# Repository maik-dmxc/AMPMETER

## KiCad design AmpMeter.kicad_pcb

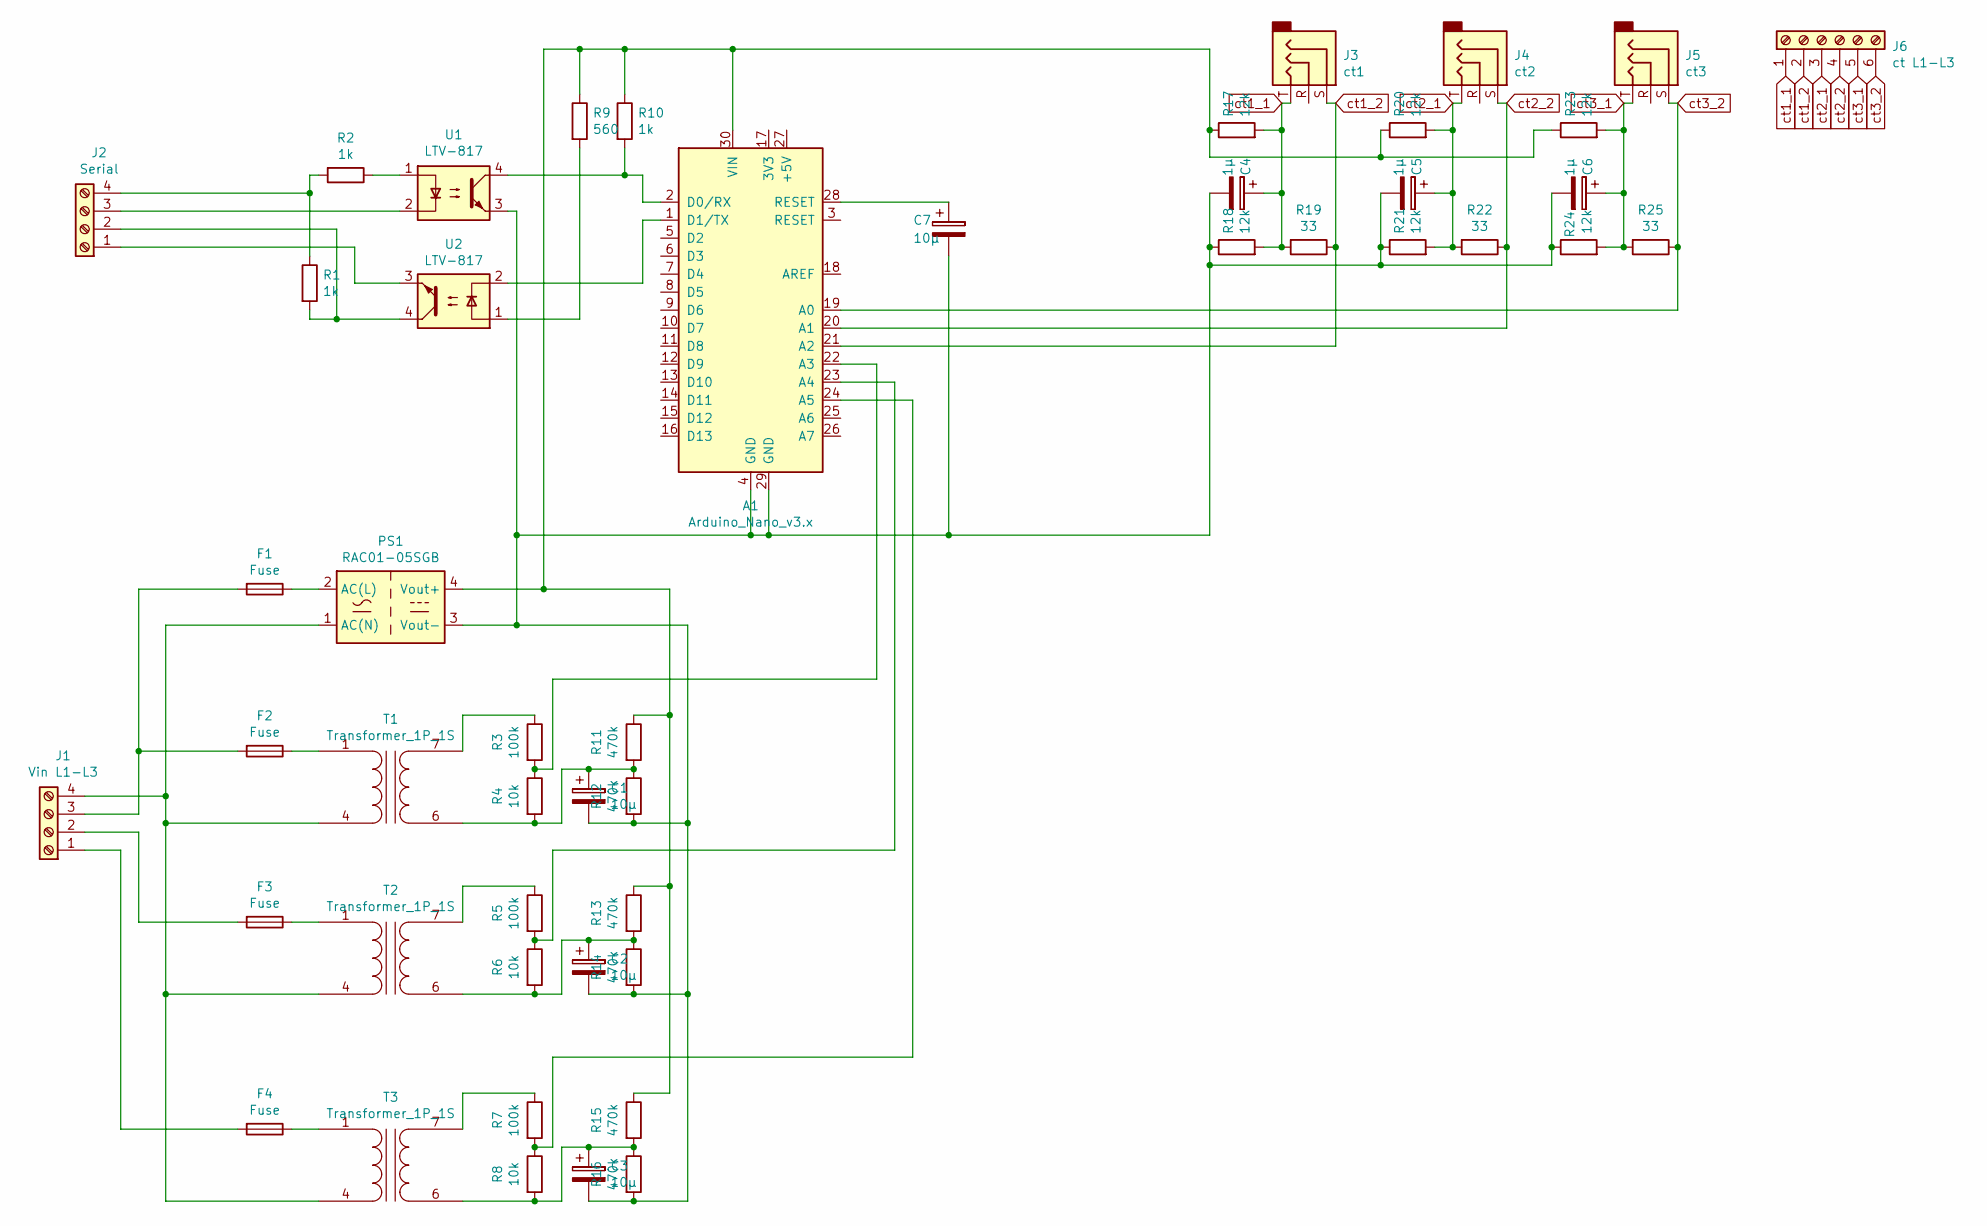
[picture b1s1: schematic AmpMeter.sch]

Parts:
A1: Arduino_Nano_v3.x; Arduino_Nano
C1, C2, C3, C7: 10µ; CP_Radial_D8.0mm_P5.00mm
C4, C5, C6: 1µ; CP_Radial_D8.0mm_P5.00mm
F1, F2, F3, F4: Fuse; Fuseholder_TR5_Littelfuse_No560_No460
J1: Vin L1-L3; TerminalBlock_Phoenix_MKDS-1,5-4_1x04_P5.00mm_Horizontal
J2: Serial; TerminalBlock_Phoenix_MKDS-1,5-4_1x04_P5.00mm_Horizontal
J3: ct1; Jack_3.5mm_Horizontal
J4: ct2; Jack_3.5mm_Horizontal
J5: ct3; Jack_3.5mm_Horizontal
J6: ct L1-L3; TerminalBlock_Phoenix_MKDS-1,5-6_1x06_P5.00mm_Horizontal
PS1: RAC01-05SGB; Converter_ACDC_HiLink_HLK-PMxx_THT
R1, R2, R10: 1k; R_1206_3216Metric
R3, R5, R7: 100k; R_1206_3216Metric
R4, R6, R8: 10k; R_1206_3216Metric
R9: 560; R_1206_3216Metric
R11, R12, R13, R14, R15, R16: 470k; R_1206_3216Metric
R17, R18, R20, R21, R23, R24: 12k; R_1206_3216Metric
R19, R22, R25: 33; R_1206_3216Metric
T1, T2, T3: Transformer_1P_1S; Transformer_Breve_TEZ-22x24
U1, U2: LTV-817; DIP-4_W7.62mm

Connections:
unnamed: A1.1 (D1/TX), U2.2
unnamed: A1.2 (D0/RX), R10.2, U1.4
unnamed: A1.22 (A3), R3.2, R4.1
unnamed: A1.23 (A4), R5.2, R6.1
unnamed: A1.24 (A5), R7.2, R8.1
unnamed: A1.28 (RESET), C7.1
unnamed: A1.4 (GND), A1.29 (GND), C1.2, C2.2, C3.2, C4.2, C5.2, C6.2, C7.2, PS1.3 (Vout-), R12.2, R14.2, R16.2, R18.1, R21.1, R24.1, U1.3
unnamed: A1.30 (VIN), PS1.4 (Vout+), R9.1, R10.1, R11.1, R13.1, R15.1, R17.1, R20.1, R23.1
unnamed: C1.1, R4.2, R11.2, R12.1, T1.6 (SA)
unnamed: C2.1, R6.2, R13.2, R14.1, T2.6 (SA)
unnamed: C3.1, R8.2, R15.2, R16.1, T3.6 (SA)
unnamed: F1.1, PS1.2 (AC(L))
unnamed: F1.2, F2.2, J1.3
unnamed: F2.1, T1.1 (AA)
unnamed: F3.1, T2.1 (AA)
unnamed: F3.2, J1.2
unnamed: F4.1, T3.1 (AA)
unnamed: F4.2, J1.1
unnamed: J1.4, PS1.1 (AC(N)), T1.4 (AB), T2.4 (AB), T3.4 (AB)
unnamed: J2.1, U2.3
unnamed: J2.2, R1.2, U2.4
unnamed: J2.3, U1.2
unnamed: J2.4, R1.1, R2.2
unnamed: R2.1, U1.1
unnamed: R3.1, T1.7 (SB)
unnamed: R5.1, T2.7 (SB)
unnamed: R7.1, T3.7 (SB)
unnamed: R9.2, U2.1
ct1_1: C4.1, J3.T, J6.1, R17.2, R18.2, R19.2
ct1_2: A1.21 (A2), J3.S, J6.2, R19.1
ct2_1: C5.1, J4.T, J6.3, R20.2, R21.2, R22.2
ct2_2: A1.20 (A1), J4.S, J6.4, R22.1
ct3_1: C6.1, J5.T, J6.5, R23.2, R24.2, R25.2
ct3_2: A1.19 (A0), J5.S, J6.6, R25.1

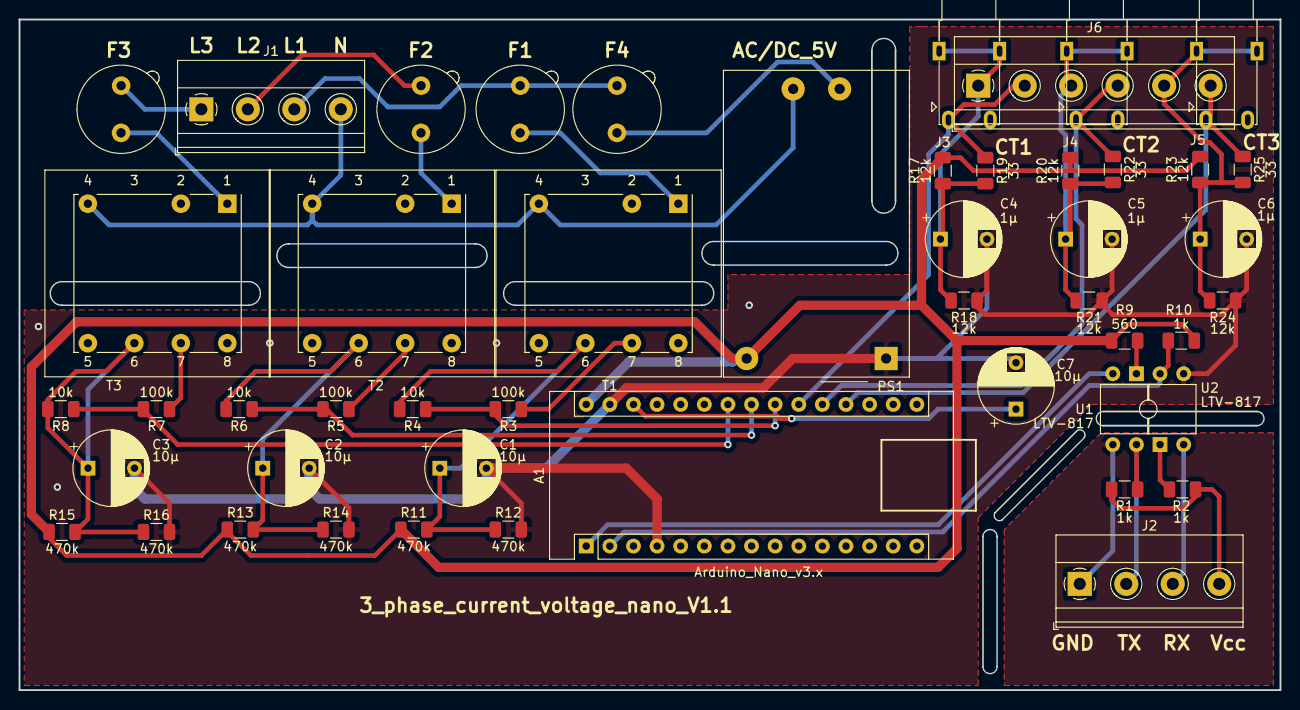
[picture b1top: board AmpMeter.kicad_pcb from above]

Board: 2 copper layers, 135.6 x 72.1 mm, 49 parts (0 on the bottom side), 34 nets.

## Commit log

2019-11-03 Add Files
2019-11-03 add sketch
2019-11-03 change values on parts
2019-11-22 add new code/fix -0.00 reading
    add reading amp -0.00
    amp < 0.01 = 0.00
    to prevent negative values
2019-11-24 add test scematics
    only test schematics for build the circuit
2020-01-24 add features
    adding float calculation of Wh
    adding kWh store into eeprom every hour
    adding read kWh from eeprom on startup
